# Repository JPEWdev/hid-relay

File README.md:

# hid-relay
Open source design for HID controlled relay

This project provides an Open Source and Open Hardware implementation of the
HID Relay board. These boards can be found for purchase from various vendors,
and appear as a USB HID device. They can be controlled using either
[pyhid-usb-relay](https://github.com/JPEWdev/pyhid-usb-relay) or
[usb-relay-hid](https://github.com/pavel-a/usb-relay-hid).

The software aims to be 100% compatible with the board that can be purchased,
allowing custom designed boards to be interchanged with the same host side
control software (and possibly to even control things other than relays).

The main controller for the relay boards is some sort of Atmel AVR chip. The
software uses the [V-USB](https://www.obdev.at/products/vusb/index.html)
project to implement the USB protocol, and should be able to run on any chip
that V-USB supports.

## Quick Install

1. Install `avrdude` (e.g. `sudo apt install avrdude`)
2. Go to the [releases](https://github.com/JPEWdev/hid-relay/releases) page and
   download the `flash.hex`, `eeprom.hex` and `fuses.txt` files for the device
   you want to program
3. Connect your AVR In System Programmer (ISP) to the relay device, and it with
   the command:
```
avrdude -P <MY_PROGRAMMER> $(cat fuses.txt)
```

4. Write the main program code and eeprom to the device by using the command:
```
avrdude -P <MY_PROGRAMMER> -p <MY_DEVICE> \
  -U flash:w:flash.hex:i \
  -U eeprom:w:eeprom.hex:i
```

## Compiling

[meson](https://mesonbuild.com/) is used as the build configuration system for
this project. In order to start compiling, you must first define a meson cross
file to tell meson about the board you are targeting. The project comes with
cross files for the included hardware designs and other platforms which can be
found in the cross/ directory. If you are using a custom hardware design, look
at these as a reference for how to define your own board.

Once you have a cross file that describes your board, configure the build with
the command:

    meson setup --cross-file path/to/my_cross.txt build

Once this is complete, the main program can be built with:

    ninja -C build

## Flashing Software

The meson configure for this project contains several convenience commands to
help program a board after the software is built. The commands use the
`avrdude` program to interact with the board. By default, meson assumes you are
using a USB AVRISP MKII programmer, but this can be changed with the
`avrdude_programmer` and `avrdude_port` meson options, for example:

    meson configure build -Davrdude_programmer=buspirate

The helper targets defined in meson are all invoked using the meson `compile`
command, like:

    meson compile -C build COMMAND

Or with ninja:

    ninja -C build COMMAND

The included commands are:

| Command           | Description                                                                       |
|-------------------|-----------------------------------------------------------------------------------|
| `writeflash`      | Write program and EEPROM memory to the device                                     |
| `writefuses`      | Write the fuse configuration to the device                                        |
| `readfuses`       | Display the current fuse configuration from the device                            |
| `readeeprom`      | Dump the current contents of the EEPROM to the file `eeprom.hex`                  |
| `readflash`       | Dump the current contents flash (program memory) to the file `flash.hex`          |
| `stats`           | Show static memory usage                                                          |
| `fuses.txt`       | Generate `fuses.txt` file which contains the `avrdude` arguments to program fuses |
| `hidrelay.asm`    | Create `hidrelay.asm` file which contains interleaved disassembly                 |

The `writefuses` command can be particularly useful to provision a new fresh
AVR, as it runs at a slow speed so it can correctly program a device even if it
is still running slowly on the internal oscillator (the default from the
factory).

Thus, to program your board after compiling, run:

    # Uncomment this line if this is a fresh chip that has never been programmed before
    # ninja -C build writefuses
    ninja -C build writeflash

**NOTE:** Be careful when programming fuses as incorrect fuses can cause the
AVR to be unprogrammable, which can only be corrected using High Voltage Serial
Programming.

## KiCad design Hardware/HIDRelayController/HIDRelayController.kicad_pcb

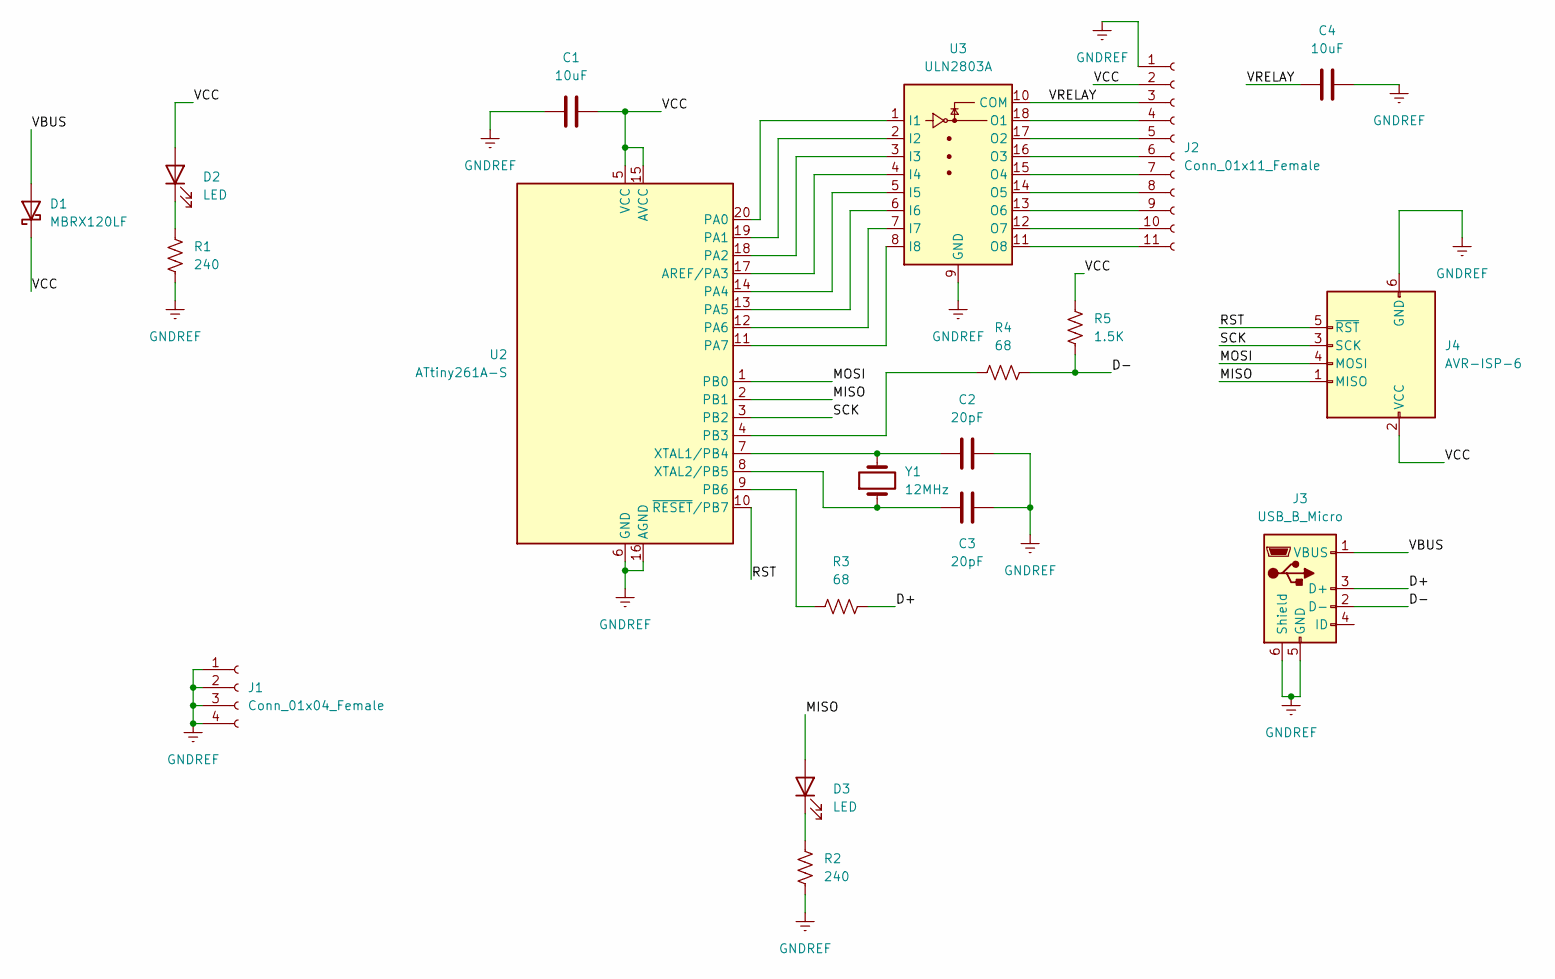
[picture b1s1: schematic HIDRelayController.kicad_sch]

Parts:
C1, C4: 10uF; C_0603_1608Metric_Pad1.08x0.95mm_HandSolder
C2, C3: 20pF; C_0603_1608Metric_Pad1.08x0.95mm_HandSolder
D1: MBRX120LF; D_SOD-123
D2, D3: LED; LED_0603_1608Metric_Pad1.05x0.95mm_HandSolder
J1: Conn_01x04_Female; PinHeader_1x04_P2.54mm_Vertical
J2: Conn_01x11_Female; PinHeader_1x11_P2.54mm_Vertical
J3: USB_B_Micro; USB_Micro-B_Wuerth_629105150521
J4: AVR-ISP-6; PinHeader_2x03_P2.54mm_Vertical
R1, R2: 240; R_0603_1608Metric_Pad0.98x0.95mm_HandSolder
R3, R4: 68; R_0603_1608Metric_Pad0.98x0.95mm_HandSolder
R5: 1.5K; R_0603_1608Metric_Pad0.98x0.95mm_HandSolder
U2: ATtiny261A-S; SOIC-20W_7.5x12.8mm_P1.27mm
U3: ULN2803A; SOIC-18W_7.5x11.6mm_P1.27mm
Y1: 12MHz; Crystal_SMD_HC49-SD_HandSoldering

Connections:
/D+: J3.3 (D+), R3.2
/D-: J3.2 (D-), R4.2, R5.1
/MISO: D3.2 (A), J4.1 (MISO), U2.2 (PB1)
/MOSI: J4.4 (MOSI), U2.1 (PB0)
/RST: J4.5 (~RST), U2.10 (~RESET/PB7)
/SCK: J4.3 (SCK), U2.3 (PB2)
/VBUS: D1.2 (A), J3.1 (VBUS)
/VCC: C1.2, D1.1 (K), D2.2 (A), J2.2, J4.2 (VCC), R5.2, U2.5 (VCC), U2.15 (AVCC)
/VRELAY: C4.1, J2.3, U3.10 (COM)
GNDREF: C1.1, C2.2, C3.2, C4.2, J1.1, J1.2, J1.3, J1.4, J2.1, J3.5 (GND), J3.6 (Shield), J4.6 (GND), R1.2, R2.2, U2.6 (GND), U2.16 (AGND), U3.9 (GND)
unnamed: C2.1, U2.7 (XTAL1/PB4), Y1.2
unnamed: C3.1, U2.8 (XTAL2/PB5), Y1.1
unnamed: D2.1 (K), R1.1
unnamed: D3.1 (K), R2.1
unnamed: J2.4, U3.18 (O1)
unnamed: J2.5, U3.17 (O2)
unnamed: J2.6, U3.16 (O3)
unnamed: J2.7, U3.15 (O4)
unnamed: J2.8, U3.14 (O5)
unnamed: J2.9, U3.13 (O6)
unnamed: J2.10, U3.12 (O7)
unnamed: J2.11, U3.11 (O8)
unnamed: R3.1, U2.9 (PB6)
unnamed: R4.1, U2.4 (PB3)
unnamed: U2.11 (PA7), U3.8 (I8)
unnamed: U2.12 (PA6), U3.7 (I7)
unnamed: U2.13 (PA5), U3.6 (I6)
unnamed: U2.14 (PA4), U3.5 (I5)
unnamed: U2.17 (AREF/PA3), U3.4 (I4)
unnamed: U2.18 (PA2), U3.3 (I3)
unnamed: U2.19 (PA1), U3.2 (I2)
unnamed: U2.20 (PA0), U3.1 (I1)

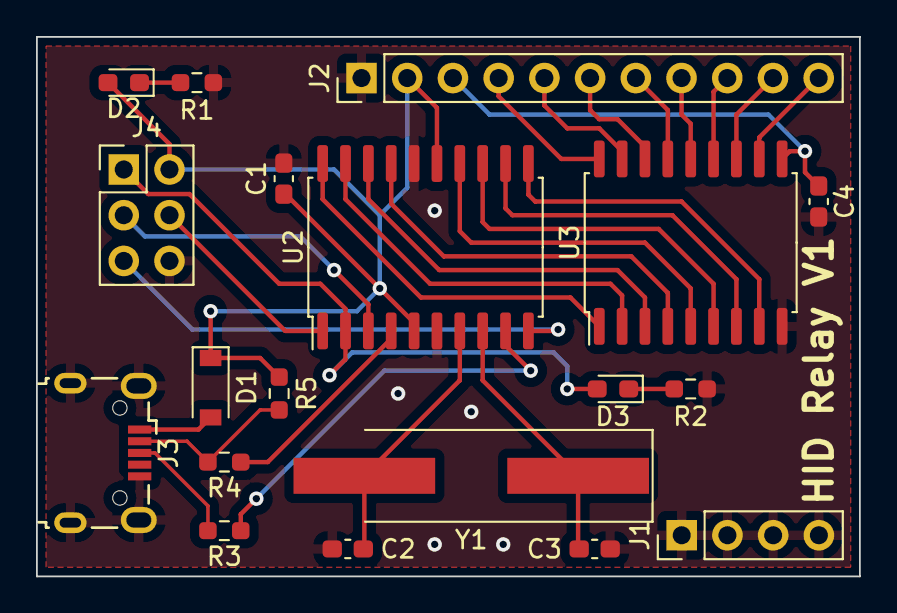
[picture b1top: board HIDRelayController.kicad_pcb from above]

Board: 2 copper layers, 45.7 x 30.0 mm, 19 parts (0 on the bottom side), 32 nets.

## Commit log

2023-03-23 Initial code
    Initial commit of the code
2023-03-23 Add HIDRelayController board
    Adds the KiCad files for the HIDRelayController board, which is a break
    out board that houses the control ATTiny216, USB connector, and drive
    chip. It can be used to drive relays or other devices.
2023-03-23 Remove HIDRelayController.xml file
    This file is only part of BOM generation, so it's not necessary to have
    in source control
2023-03-25 Add stats target
    Adds a `stats` target which shows the static memory usage of the
    program.
2023-03-25 README: ninja can be used to invoke helper targets
2023-03-25 meson: Save map file when linking
    Saves off the map file when linking, which is useful to track memory
    usage
2023-03-25 Move relay and led IO config to cross file
    Moves the configuration about which IO port the relays and LED are
    located on to the cross file so different boards can configure it
    appropriately
2023-03-25 Add option to report relay serial as USB serial
    The original behavior of the relays reports a blank USB serial number,
    with the only way to get the serial number being through the HID
    interface. This is undesirable when multiple boards are connected, as it
    makes it hard to distinguish between boards. This optional feature makes
    the software report the HID serial number as the USB serial number also,
    but comes at the cost of more RAM usage, code space, and deviating from
2023-03-25 meson: Add readflash target
    Adds a target to read the flash back from the device and save it to a
    file
2023-03-26 Allow LED to be optional
2023-03-26 meson: Use integers instead of strings in cross file
    Converts values which are actually integers to be integers in the cross
    file, and adds additional validation checking.
2023-03-26 meson: Change default warning level to 3
    Bumps up the default warning level from 1 to 3 (pedanticour )
2023-03-26 Split out relay driver from main code
    Splits out the code that controls how relays are turned on and off into
    a separate file. This will allow alternate drivers in the future.
    Currently, the only driver is the "simple" driver that keeps the
    existing behavior.
2023-03-26 Allow watchdog to be optional
    Adds a cross option to disable the watchdog, in case it doesn't fit on
    really small devices
2023-03-26 meson: Add option for cross file to set interrupt config
    Adds support for the cross file to specify the V-USB interrupt
    configuration, in case it's not the default of INT0
2023-04-06 drivers: simple: Add offset
    Adds an offest property to indicate where in the output I/O port the
    relays start, if not 0
2023-04-06 HIDRelayController: Fix endian-ness
    'none' is not a valid endian-ness, and AVR devices are little endian
    anyway.
2023-04-06 hardware: HIDRelayController: Remove silly via
    No point in having a via for VRELAY right next to the PTH
2023-04-06 Fix USB request type
    The USB request type is CLASS, not VENDOR
2023-04-06 HIDRelayController: Don't always enable watchdog
    Disables the watchdog being forced on since it is not enabled on this
    device.
2023-04-06 Fix serial length
    The length of the serial number is 5 bytes, not 6. Also, when reporting
    the serial number as a USB string, each character is 2 bytes instead of
    1 and the header length needs to be included, so fix that also
2023-04-06 Optimize relay commands
    Combining the handling of the on and off command saves 12 bytes of space
2023-04-06 Relays are 1-indexed
    The first relay in the HID API is relay 1, not 0
2023-04-06 Fix USB Device ID
    The USB device ID should be 0x05df to match the dcttech software and be
    detected by the PC tools.
2023-04-06 Fix set serial command
    The serial number starts at the second byte of the packet, not the first
2023-04-06 meson: Allow efuses to be optional
    Not all AVR chips have efuses
2023-04-06 Add dcttech 8 channel relay
    Adds a cross file to build alternate firmware for the dcttech 8 channel
    relay.
2023-04-07 Replace dcttech driver with alacarte
    Replaces the dcttech specific driver with a more generic one that can do
    the same thing, named alacarte
2023-04-07 Add github workflow to build devices
2023-04-07 Reformat with clang-format
2023-04-07 Check formatting in build workflow
2023-04-07 alacarte: Fix relay 3 and simplify
    Fixes the relay 3 definition which was incorrectly using the wrong bit,
    and simplify the way relays are defined to remove the need for the
    intermediate RELAY_n_(PORT,DDR,MASK) defines
2023-04-07 GitHub actions: Build for other attinyX61 variants
    The hardware can be built with any of the attiny[248]61 chips, so build
    the software for all of them
2023-04-07 Add script to generate fuse command line for avrdude
    Adds a script which can be used to generate an appropriate command line
    to write fuses using avrdude
2023-04-11 Add LED helpers
    Adds helper macros to turn the LED on, off and toggle
2023-04-11 Add oscillator calibration
    Some devices use an internal oscillator instead of a crystal; these
    devices need to have the oscillator calibrated in order to properly
    function, so add support for enabling this in the cross file
2023-04-11 Add dcttech 2 channel relay
    Adds support for building firmware for the dcttech 2 channel relay
    I was also able to pull the original firmware off of this one, so it is
    provided as backup in case you want to restore the original using
    avrdude
2023-04-12 github actions: Add steps to release artifacts
    Adds steps to the build to push the built artifacts when releasing
2023-04-12 Add dissassembly command
    Add a build target to disassemble program for inspection
2023-04-12 README.md: Add quick install guide
    Adds a quick install guide the explains how to flash a device from a
    release
2023-10-27 Update README.md
    Fix the flashing instructions
2023-10-27 Fix USB config for Windows
    Windows is a little more picky about the USB configuration making sense
    than Linux, so fix a few of the settings to make it report properly
2023-10-27 Pass separate part to avrdude
    Older versions of avrdude do not accept the same CPU strings as GCC, and
    thus must use the older names to program devices
2023-10-27 Disable USB serial ID on ATTiny261
    Its just too small for the serial number code with the new USB
    configuration options
2023-10-29 Disable interrupt code
    While the interrupt end point needs to be defined, we don't need the
    code to actually do anything.
2024-05-10 Add CRC check
    Adds a check to validate the CRC of all received packets. This is too
    late to ignore the packet as V-USB has already sent the ACK, but it will
    prevent the relay from operating on bad data.
2024-05-10 Add option to use fast CRC
    Adds an option to use the fast CRC code (which is larger)
2024-05-10 cross: Enable CRC checking
    Enables CRC checking for all boards
2024-05-10 Report version in USB descriptor
    Reports the software version in the USB descriptor
2024-05-10 Eliminate data input buffering
    There is no reason to buffer multiple data packets as short packets are
    not seen in practice.
2024-05-10 Use eeprom_update_block() for serial
    Reduces wear on flash if the serial isn't actually changed
2024-05-13 Optimize calibration routine
    Optimizes the internal oscillator calibration routine to:
    1) Use 6 clock cycles per timing loop instead of 7 for increased
    accuracy
    2) Test the high and low ranges of OSCCAL for devices that support it
2024-05-14 Force clock to 12.8 MHz or 16.5 MHz with internal oscillator
    If the internal oscillator is used, the clock frequency must be 12.8 MHz
    or 16.5 MHz to work properly with V-USB. Validate this at configure
    time.
    The dcttech 2 channel USB relay uses the internal oscillator, so fix it
    accordingly.
2024-05-20 Bump version for release
